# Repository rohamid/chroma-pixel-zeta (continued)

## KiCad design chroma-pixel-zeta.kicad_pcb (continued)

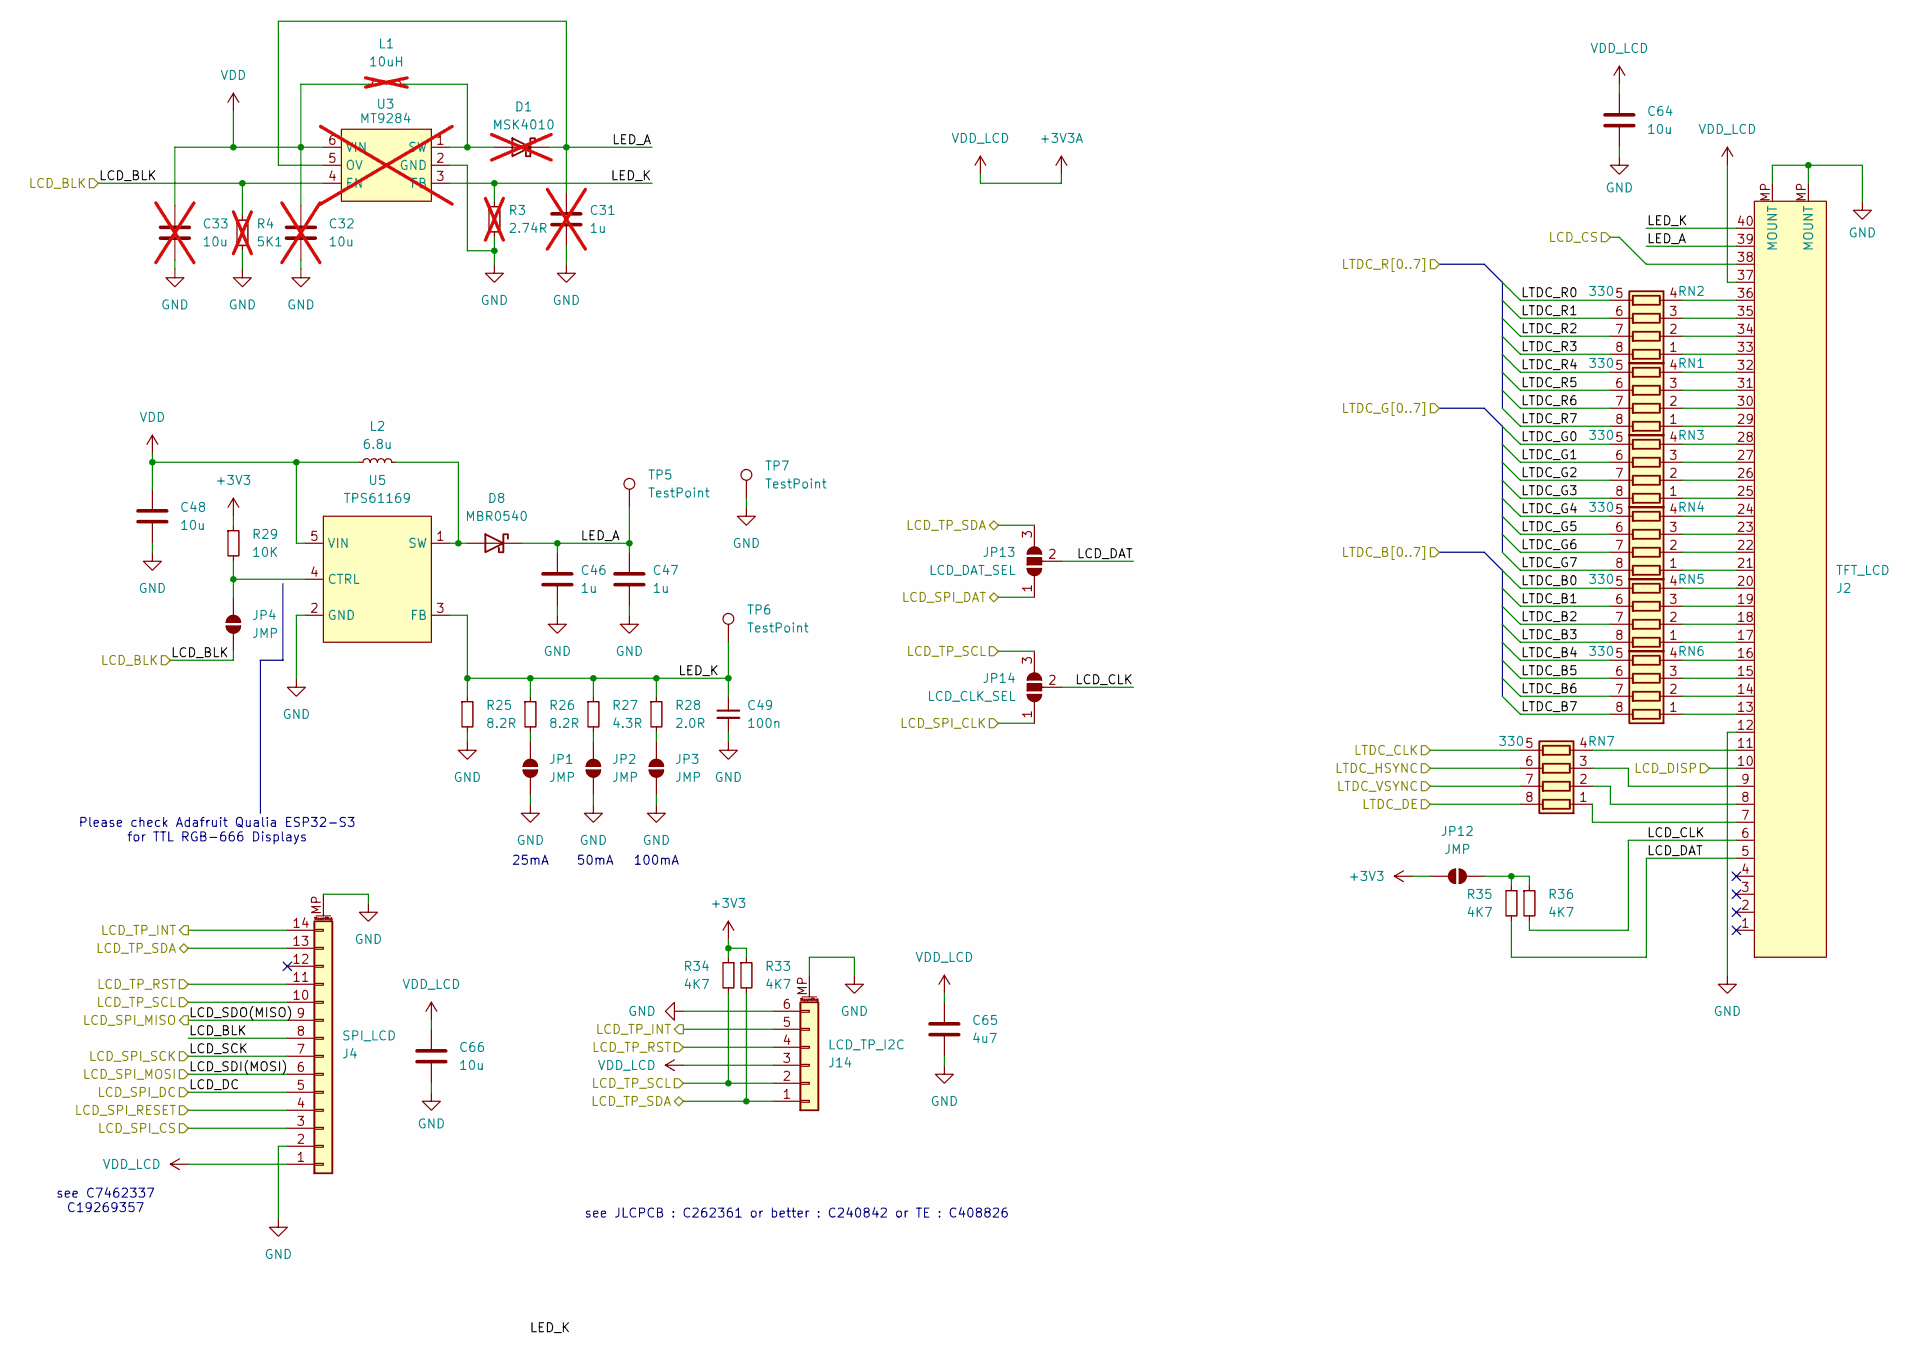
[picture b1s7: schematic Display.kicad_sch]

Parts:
C31: 1u; C_0603_1608Metric; JLCPCB Part # C15849; not fitted
C32, C33: 10u; C_0603_1608Metric; JLCPCB Part # C96446; not fitted
C46, C47: 1u; C_0603_1608Metric; JLCPCB Part # C15849
C48, C64, C66: 10u; C_0603_1608Metric; JLCPCB Part # C96446
C49: 100n; C_0402_1005Metric; JLCPCB Part # C307331
C65: 4u7; C_0603_1608Metric; JLCPCB Part # C19666
D1: MSK4010; D_SOD-523; JLCPCB Part # C345958; not fitted
D8: MBR0540; D_SOD-123; JLCPCB Part # C21353
J2: TFT_LCD; Omron-XF2M-4015-1A-R100-0-0-0; JLCPCB Part # C225713
J4: SPI_LCD; FPC-14P-1mm-XUNPU; JLCPCB Part # C19269357
J14: LCD_TP_I2C; TE_84952-6_1x06-1MP_P1.0mm_Horizontal; JLCPCB Part # C408826
JP1, JP2, JP3, JP4, JP12: JMP; SolderJumper-2_P1.3mm_Open_RoundedPad1.0x1.5mm
JP13: LCD_DAT_SEL; SolderJumper-3_P1.3mm_Open_RoundedPad1.0x1.5mm_NumberLabels
JP14: LCD_CLK_SEL; SolderJumper-3_P1.3mm_Open_RoundedPad1.0x1.5mm_NumberLabels
L1: 10uH; L_1210_3225Metric; JLCPCB Part # C189932; not fitted
L2: 6.8u; L_1210_3225Metric; JLCPCB Part # C844992
R3: 2.74R; R_0402_1005Metric; JLCPCB Part # C166483; not fitted
R4: 5K1; R_0402_1005Metric; JLCPCB Part # C25905; not fitted
R25, R26: 8.2R; R_0402_1005Metric; JLCPCB Part # C514788
R27: 4.3R; R_0402_1005Metric; JLCPCB Part # C166641
R28: 2.0R; R_0402_1005Metric; JLCPCB Part # C203084
R29: 10K; R_0402_1005Metric; JLCPCB Part # C25744
R33, R34, R35, R36: 4K7; R_0402_1005Metric; JLCPCB Part # C203084
RN1, RN2, RN3, RN4, RN5, RN6, RN7: 330; R_Array_Convex_4x0603; JLCPCB Part # C12018
TP5, TP6, TP7: TestPoint; TestPoint_Pad_D1.5mm
U3: MT9284; SOT-23-6; JLCPCB Part # C181780; not fitted
U5: TPS61169; SOT-353_SC-70-5; JLCPCB Part # C71045

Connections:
+3V3: JP12.2 (B), R29.1, R33.1, R34.1; also elsewhere on the board
+3V3A: C64.1, C65.1, C66.1, J2.37, J4.1, J14.3; also elsewhere on the board
/LCD/LCD_BLK: J4.8, JP4.1 (A), R4.1, U3.4 (EN); also elsewhere on the board
/LCD/LCD_CLK: J2.6, JP14.2 (C), R36.2
/LCD/LCD_CS: J2.38; also elsewhere on the board
/LCD/LCD_DAT: J2.5, JP13.2 (C), R35.2
/LCD/LCD_DC: J4.5; also elsewhere on the board
/LCD/LCD_DISP: J2.10; also elsewhere on the board
/LCD/LCD_SCK: J4.7; also elsewhere on the board
/LCD/LCD_SDI(MOSI): J4.6; also elsewhere on the board
/LCD/LCD_SDO(MISO): J4.9; also elsewhere on the board
/LCD/LCD_SPI_CLK: JP14.1 (A); also elsewhere on the board
/LCD/LCD_SPI_CS: J4.3; also elsewhere on the board
/LCD/LCD_SPI_DAT: JP13.1 (A); also elsewhere on the board
/LCD/LCD_SPI_RESET: J4.4; also elsewhere on the board
/LCD/LCD_TP_INT: J4.14, J14.5; also elsewhere on the board
/LCD/LCD_TP_RST: J4.11, J14.4; also elsewhere on the board
/LCD/LCD_TP_SCL: J4.10, J14.2, JP14.3 (B), R34.2; also elsewhere on the board
/LCD/LCD_TP_SDA: J4.13, J14.1, JP13.3 (B), R33.2; also elsewhere on the board
/LCD/LED_A: C31.1, C46.1, C47.1, D1.1 (K), D8.1 (K), J2.39, TP5.1, U3.5 (OV)
/LCD/LED_K: C49.1, J2.40, R3.1, R25.1, R26.1, R27.1, R28.1, TP6.1, U3.3 (FB), U5.3 (FB)
/LCD/LTDC_B0: RN5.5 (R4.2); also elsewhere on the board
/LCD/LTDC_B1: RN5.6 (R3.2); also elsewhere on the board
/LCD/LTDC_B2: RN5.7 (R2.2); also elsewhere on the board
/LCD/LTDC_B3: RN5.8 (R1.2); also elsewhere on the board
/LCD/LTDC_B4: RN6.5 (R4.2); also elsewhere on the board
/LCD/LTDC_B5: RN6.6 (R3.2); also elsewhere on the board
/LCD/LTDC_B6: RN6.7 (R2.2); also elsewhere on the board
/LCD/LTDC_B7: RN6.8 (R1.2); also elsewhere on the board
/LCD/LTDC_CLK: RN7.5 (R4.2); also elsewhere on the board
/LCD/LTDC_DE: RN7.8 (R1.2); also elsewhere on the board
/LCD/LTDC_G0: RN3.5 (R4.2); also elsewhere on the board
/LCD/LTDC_G1: RN3.6 (R3.2); also elsewhere on the board
/LCD/LTDC_G2: RN3.7 (R2.2); also elsewhere on the board
/LCD/LTDC_G3: RN3.8 (R1.2); also elsewhere on the board
/LCD/LTDC_G4: RN4.5 (R4.2); also elsewhere on the board
/LCD/LTDC_G5: RN4.6 (R3.2); also elsewhere on the board
/LCD/LTDC_G6: RN4.7 (R2.2); also elsewhere on the board
/LCD/LTDC_G7: RN4.8 (R1.2); also elsewhere on the board
/LCD/LTDC_HSYNC: RN7.6 (R3.2); also elsewhere on the board
/LCD/LTDC_R0: RN2.5 (R4.2); also elsewhere on the board
/LCD/LTDC_R1: RN2.6 (R3.2); also elsewhere on the board
/LCD/LTDC_R2: RN2.7 (R2.2); also elsewhere on the board
/LCD/LTDC_R3: RN2.8 (R1.2); also elsewhere on the board
/LCD/LTDC_R4: RN1.5 (R4.2); also elsewhere on the board
/LCD/LTDC_R5: RN1.6 (R3.2); also elsewhere on the board
/LCD/LTDC_R6: RN1.7 (R2.2); also elsewhere on the board
/LCD/LTDC_R7: RN1.8 (R1.2); also elsewhere on the board
/LCD/LTDC_VSYNC: RN7.7 (R2.2); also elsewhere on the board
GND: C31.2, C32.2, C33.2, C46.2, C47.2, C48.2, C49.2, C64.2, C65.2, C66.2, J2.12, J2.MP (MOUNT), J4.2, J4.MP (MountPin), J14.6, J14.MP (MountPin), JP1.1 (A), JP2.1 (A), JP3.1 (A), R3.2, R4.2, R25.2, TP7.1, U3.2 (GND), U5.2 (GND); also elsewhere on the board
unnamed: D1.2 (A), L1.2, U3.1 (SW)
unnamed: D8.2 (A), L2.2, U5.1 (SW)
unnamed: JP1.2 (B), R26.2
unnamed: JP2.2 (B), R27.2
unnamed: JP3.2 (B), R28.2
unnamed: JP4.2 (B), R29.2, U5.4 (CTRL)
unnamed: JP12.1 (A), R35.1, R36.1
unnamed: J2.29, RN1.1 (R1.1)
unnamed: J2.30, RN1.2 (R2.1)
unnamed: J2.31, RN1.3 (R3.1)
unnamed: J2.32, RN1.4 (R4.1)
unnamed: J2.33, RN2.1 (R1.1)
unnamed: J2.34, RN2.2 (R2.1)
unnamed: J2.35, RN2.3 (R3.1)
unnamed: J2.36, RN2.4 (R4.1)
unnamed: J2.25, RN3.1 (R1.1)
unnamed: J2.26, RN3.2 (R2.1)
unnamed: J2.27, RN3.3 (R3.1)
unnamed: J2.28, RN3.4 (R4.1)
unnamed: J2.21, RN4.1 (R1.1)
unnamed: J2.22, RN4.2 (R2.1)
unnamed: J2.23, RN4.3 (R3.1)
unnamed: J2.24, RN4.4 (R4.1)
unnamed: J2.17, RN5.1 (R1.1)
unnamed: J2.18, RN5.2 (R2.1)
unnamed: J2.19, RN5.3 (R3.1)
unnamed: J2.20, RN5.4 (R4.1)
unnamed: J2.13, RN6.1 (R1.1)
unnamed: J2.14, RN6.2 (R2.1)
unnamed: J2.15, RN6.3 (R3.1)
unnamed: J2.16, RN6.4 (R4.1)
unnamed: J2.7, RN7.1 (R1.1)
unnamed: J2.8, RN7.2 (R2.1)
unnamed: J2.9, RN7.3 (R3.1)
unnamed: J2.11, RN7.4 (R4.1)
VDD: C32.1, C33.1, C48.1, L1.1, L2.1, U3.6 (VIN), U5.5 (VIN); also elsewhere on the board

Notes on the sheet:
100mA
see C7462337 C19269357
see JLCPCB : C262361 or better : C240842 or TE : C408826
50mA
25mA
Please check Adafruit Qualia ESP32-S3 for TTL RGB-666 Displays

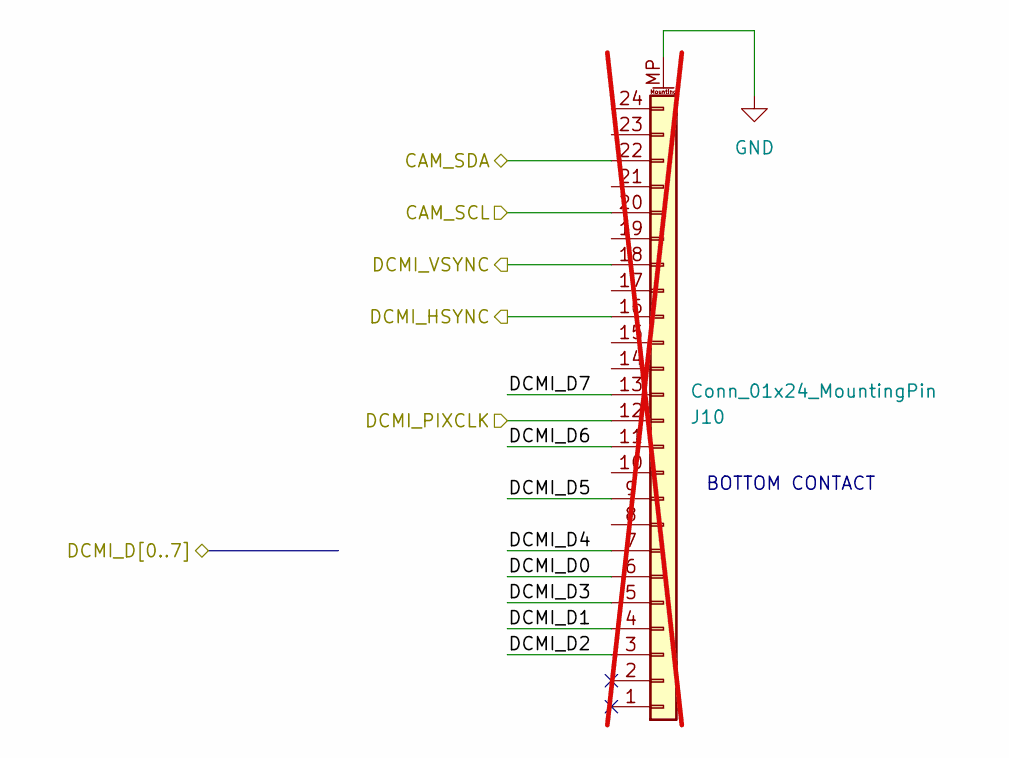
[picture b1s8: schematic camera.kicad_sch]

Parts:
J10: Conn_01x24_MountingPin; Jushuo_AFC07-S24FCA-00_1x24-1MP_P0.50_Horizontal; JLCPCB Part # C262567; not fitted

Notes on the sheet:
BOTTOM CONTACT

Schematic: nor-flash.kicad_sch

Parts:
C21, C22: 100n; C_0402_1005Metric; JLCPCB Part # C307331
JP8: FLASH_CONFIG; SolderJumper-3_P1.3mm_Open_RoundedPad1.0x1.5mm_NumberLabels
JP9: FLASH_EN; SolderJumper-2_P1.3mm_Open_RoundedPad1.0x1.5mm
R1, R2: 10K; R_0402_1005Metric; JLCPCB Part # C25744
U1, U4: MT25Q; WSON-8-1EP_8x6mm_P1.27mm_EP3.4x4.3mm; JLCPCB Part # C2061007

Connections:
+3V3: C21.1, JP9.2 (B), R1.1, R2.1, U1.8 (VCC); also elsewhere on the board
/MCU/QUADSPI_BK1_IO0: U1.5 (DI(IO0)); also elsewhere on the board
/MCU/QUADSPI_BK1_IO1: U1.2 (DO(IO1)); also elsewhere on the board
/MCU/QUADSPI_BK1_IO2: U1.3 (IO2); also elsewhere on the board
/MCU/QUADSPI_BK1_IO3: U1.7 (IO3); also elsewhere on the board
/MCU/QUADSPI_BK1_NCS: JP8.3 (B), R1.2, U1.1 (~CS); also elsewhere on the board
/MCU/QUADSPI_BK2_IO0: U4.5 (DI(IO0)); also elsewhere on the board
/MCU/QUADSPI_BK2_IO1: U4.2 (DO(IO1)); also elsewhere on the board
/MCU/QUADSPI_BK2_IO2: U4.3 (IO2); also elsewhere on the board
/MCU/QUADSPI_BK2_IO3: U4.7 (IO3); also elsewhere on the board
/MCU/QUADSPI_BK2_NCS: JP8.1 (A); also elsewhere on the board
/MCU/QUADSPI_CLK: U1.6 (CLK), U4.6 (CLK); also elsewhere on the board
GND: C21.2, C22.2, U1.4 (GND), U1.9 (EP), U4.4 (GND), U4.9 (EP); also elsewhere on the board
unnamed: JP8.2 (C), R2.2, U4.1 (~CS)
unnamed: C22.1, JP9.1 (A), U4.8 (VCC)

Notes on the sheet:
NOR FLASH

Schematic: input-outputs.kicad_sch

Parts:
C67: 10u; C_0603_1608Metric; JLCPCB Part # C96446
D9: ESDA14V2L; SOT-23; JLCPCB Part # C343996
D10: NSR0320MW2T1G; D_SOD-323; JLCPCB Part # C48192
J5: I2C-STEMMA-QT; JST_SM04B-SRSS-TB_LF__SN_; JLCPCB Part # C160404
J7: swd; PinHeader_2x07_P1.27mm_Vertical_SMD; JLCPCB Part # C2881912
J9: UART; Hirose_DF13C_CL535-0404-8-51_1x04-1MP_P1.25mm_Vertical; JLCPCB Part # C7430470
NT1: NetTie_2; NetTie-2_SMD_Pad0.5mm

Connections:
+3V3: C67.1, J5.3, J7.3; also elsewhere on the board
+5V: J9.1, NT1.2; also elsewhere on the board
/IO/DBG_RX: J7.13; also elsewhere on the board
/IO/DBG_SWCLK: J7.6; also elsewhere on the board
/IO/DBG_SWDIO: J7.4; also elsewhere on the board
/IO/DBG_SWO: J7.8; also elsewhere on the board
/IO/DBG_TX: J7.14; also elsewhere on the board
/IO/STEMMA_SCL: J5.1; also elsewhere on the board
/IO/STEMMA_SDA: J5.2; also elsewhere on the board
/IO/USART6_RX: D9.1 (K), J9.2; also elsewhere on the board
/IO/USART6_TX: D9.2 (K), J9.3; also elsewhere on the board
/MCU/NRST: J7.12; also elsewhere on the board
GND: C67.2, D9.3 (A), J5.4, J5.S1 (SHIELD), J5.S2 (SHIELD), J7.2, J7.5, J7.7, J9.4, J9.MP (MountPin); also elsewhere on the board
unnamed: D10.2 (A), J7.1
VBUS: NT1.1; also elsewhere on the board
VDD: D10.1 (K); also elsewhere on the board

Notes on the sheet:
TO MCU TX
TO MCU RX

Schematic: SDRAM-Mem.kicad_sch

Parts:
C1, C2, C3, C29, C36, C37, C38: 100n; C_0402_1005Metric; JLCPCB Part # C307331
U9: MT48LC16M16A2P; TSOP-II-54_22.2x10.16mm_P0.8mm; JLCPCB Part # C412833

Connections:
+3V3: C1.1, C2.1, C3.1, C29.1, C36.1, C37.1, C38.1, U9.1 (VDD), U9.3 (VDDQ), U9.9 (VDDQ), U9.14 (VDD), U9.27 (VDD), U9.43 (VDDQ), U9.49 (VDDQ); also elsewhere on the board
/MCU/SDRAM_ADD0: U9.23 (A0); also elsewhere on the board
/MCU/SDRAM_ADD1: U9.24 (A1); also elsewhere on the board
/MCU/SDRAM_ADD2: U9.25 (A2); also elsewhere on the board
/MCU/SDRAM_ADD3: U9.26 (A3); also elsewhere on the board
/MCU/SDRAM_ADD4: U9.29 (A4); also elsewhere on the board
/MCU/SDRAM_ADD5: U9.30 (A5); also elsewhere on the board
/MCU/SDRAM_ADD6: U9.31 (A6); also elsewhere on the board
/MCU/SDRAM_ADD7: U9.32 (A7); also elsewhere on the board
/MCU/SDRAM_ADD8: U9.33 (A8); also elsewhere on the board
/MCU/SDRAM_ADD9: U9.34 (A9); also elsewhere on the board
/MCU/SDRAM_ADD10: U9.22 (A10); also elsewhere on the board
/MCU/SDRAM_ADD11: U9.35 (A11); also elsewhere on the board
/MCU/SDRAM_ADD12: U9.36 (A12); also elsewhere on the board
/MCU/SDRAM_DQ0: U9.2 (DQ0); also elsewhere on the board
/MCU/SDRAM_DQ1: U9.4 (DQ1); also elsewhere on the board
/MCU/SDRAM_DQ2: U9.5 (DQ2); also elsewhere on the board
/MCU/SDRAM_DQ3: U9.7 (DQ3); also elsewhere on the board
/MCU/SDRAM_DQ4: U9.8 (DQ4); also elsewhere on the board
/MCU/SDRAM_DQ5: U9.10 (DQ5); also elsewhere on the board
/MCU/SDRAM_DQ6: U9.11 (DQ6); also elsewhere on the board
/MCU/SDRAM_DQ7: U9.13 (DQ7); also elsewhere on the board
/MCU/SDRAM_DQ8: U9.42 (DQ8); also elsewhere on the board
/MCU/SDRAM_DQ9: U9.44 (DQ9); also elsewhere on the board
/MCU/SDRAM_DQ10: U9.45 (DQ10); also elsewhere on the board
/MCU/SDRAM_DQ11: U9.47 (DQ11); also elsewhere on the board
/MCU/SDRAM_DQ12: U9.48 (DQ12); also elsewhere on the board
/MCU/SDRAM_DQ13: U9.50 (DQ13); also elsewhere on the board
/MCU/SDRAM_DQ14: U9.51 (DQ14); also elsewhere on the board
/MCU/SDRAM_DQ15: U9.53 (DQ15); also elsewhere on the board
/MEMORY SDRAM/SDRAM_BA0: U9.20 (BA0); also elsewhere on the board
/MEMORY SDRAM/SDRAM_BA1: U9.21 (BA1); also elsewhere on the board
/MEMORY SDRAM/SDRAM_CKE: U9.37 (CKE); also elsewhere on the board
/MEMORY SDRAM/SDRAM_CLK: U9.38 (CLK); also elsewhere on the board
/MEMORY SDRAM/SDRAM_LDQM: U9.15 (DQML); also elsewhere on the board
/MEMORY SDRAM/SDRAM_UDQM: U9.39 (DQMH); also elsewhere on the board
/MEMORY SDRAM/~SDRAM_CAS: U9.17 (~CAS); also elsewhere on the board
/MEMORY SDRAM/~SDRAM_CS: U9.19 (~CS); also elsewhere on the board
/MEMORY SDRAM/~SDRAM_RAS: U9.18 (~RAS); also elsewhere on the board
/MEMORY SDRAM/~SDRAM_WE: U9.16 (~WE); also elsewhere on the board
GND: C1.2, C2.2, C3.2, C29.2, C36.2, C37.2, C38.2, U9.6 (VSSQ), U9.12 (VSSQ), U9.28 (VSS), U9.41 (VSS), U9.46 (VSSQ), U9.52 (VSSQ), U9.54 (VSS); also elsewhere on the board

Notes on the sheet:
or IS42S16160J-7TL
C412833

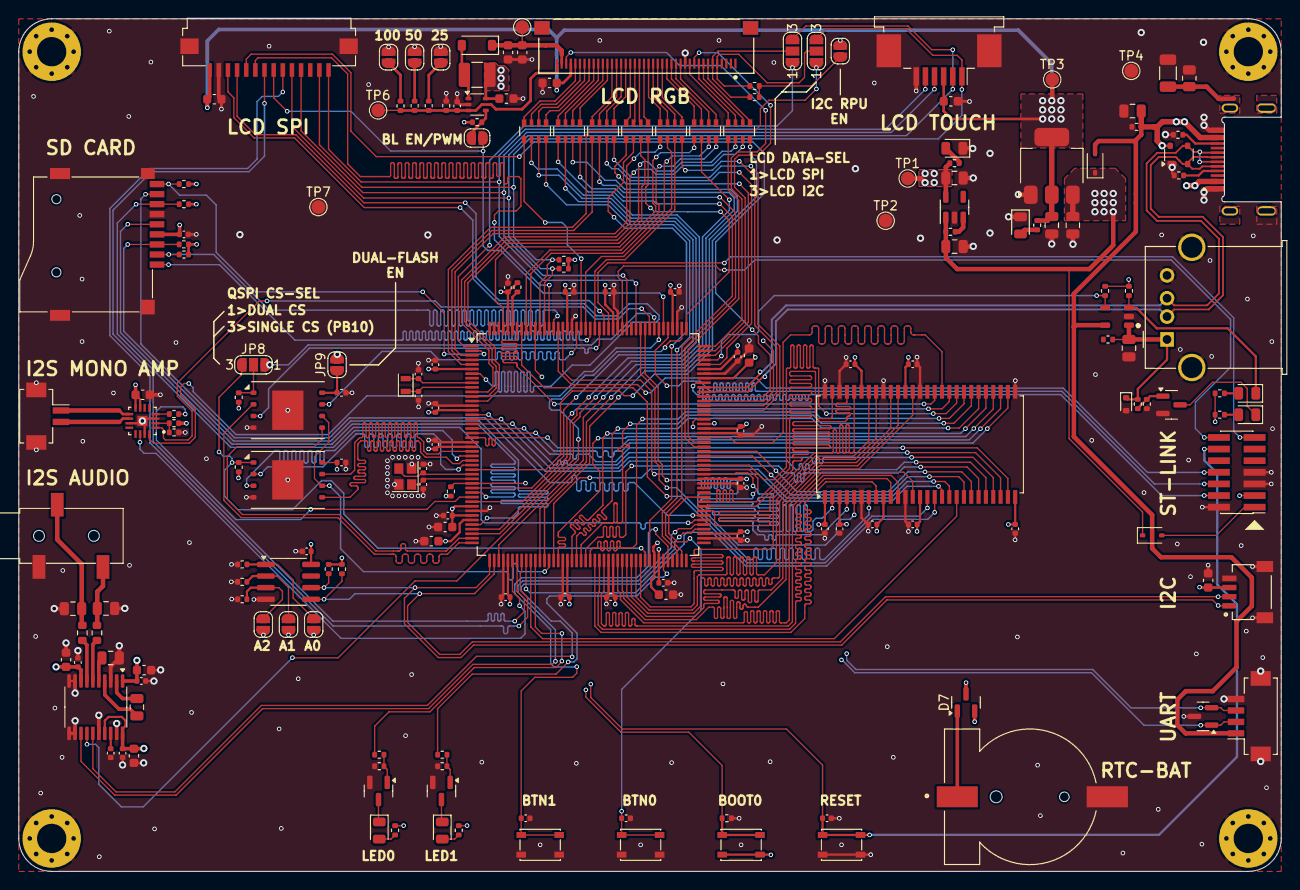
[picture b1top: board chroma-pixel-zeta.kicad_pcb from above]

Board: 4 copper layers, 138.0 x 93.2 mm, 190 parts (0 on the bottom side), 213 nets.

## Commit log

2024-07-09 Change MCU to STM32H743IIT6
2024-07-09 Cleaning schematic, added more independently schematics
2024-07-10 Layout SDRAM
2024-07-10 relayout SDRAM
2024-07-11 Finished SDRAM, QSPI Flash, Planning to move to 5 inch orient display dimension
2024-07-11 Move to 5 inch dimension
2024-07-11 finished layout backlight driver
2024-07-12 Changes: USB C to midmount, CR1220 socket, flip MCU to shorten the LCD traces
2024-07-14 Finished SDRAM, LTDC, QSPI, SDMMC, still an error on LTDC B channel
2024-07-14 Finished SDRAM, QSPI, SDMMC, LTDC, TP, EEPROM, USB, debug (need to verify on UART)
2024-07-16 via changed to 0.3/0.5
2024-07-16 not yet
2024-07-17 Button, LED, i2s audio, LCD & SD ctrl left
2024-07-17 Almost finished
2024-07-18 Still on progress...
2024-07-18 Removing Camera, create alternative footprint for SPI LCD conn
2024-07-19 First release
